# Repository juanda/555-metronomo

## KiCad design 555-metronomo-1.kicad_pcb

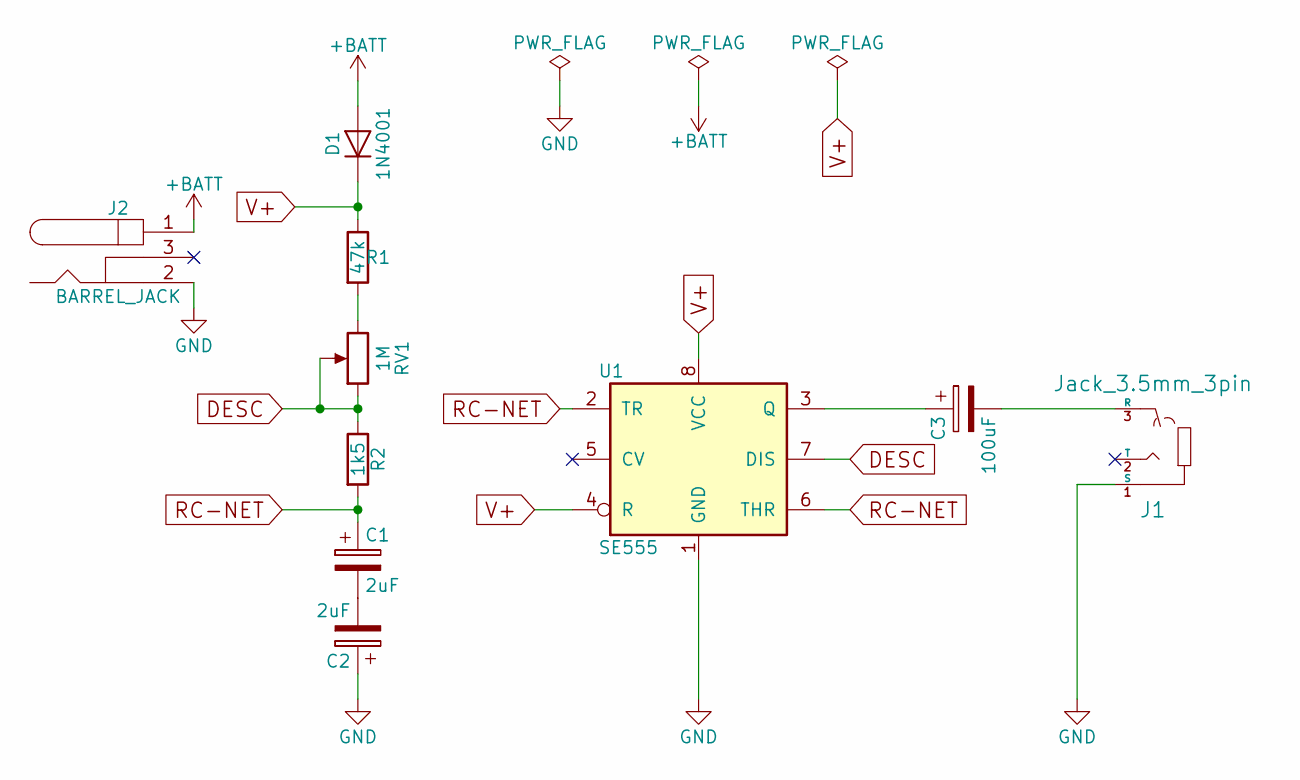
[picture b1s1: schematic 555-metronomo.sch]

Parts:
C1, C2: 2uF; CP_Axial_L18.0mm_D6.5mm_P25.00mm_Horizontal
C3: 100uF; CP_Axial_L34.5mm_D20.0mm_P41.00mm_Horizontal
D1: 1N4001; D_DO-41_SOD81_P5.08mm_Vertical_AnodeUp
J1: Jack_3.5mm_3pin; BARREL_JACK
J2: BARREL_JACK
R1: 47k; R_Axial_DIN0204_L3.6mm_D1.6mm_P1.90mm_Vertical
R2: 1k5; R_Axial_DIN0204_L3.6mm_D1.6mm_P1.90mm_Vertical
RV1: 1M; Potentiometer_Alps_RK09K_Horizontal
U1: SE555; DIP-8_W7.62mm

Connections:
+BATT: D1.2 (A), J2.1
DESC: R2.1, RV1.1, RV1.2, U1.7 (DIS)
GND: C2.1, J1.1 (S), J2.2, U1.1 (GND)
unnamed: C1.2, C2.2
unnamed: C3.1, U1.3 (Q)
unnamed: C3.2, J1.3 (R)
unnamed: R1.2, RV1.3
RC-NET: C1.1, R2.2, U1.2 (TR), U1.6 (THR)
V+: D1.1 (K), R1.1, U1.4 (R), U1.8 (VCC)

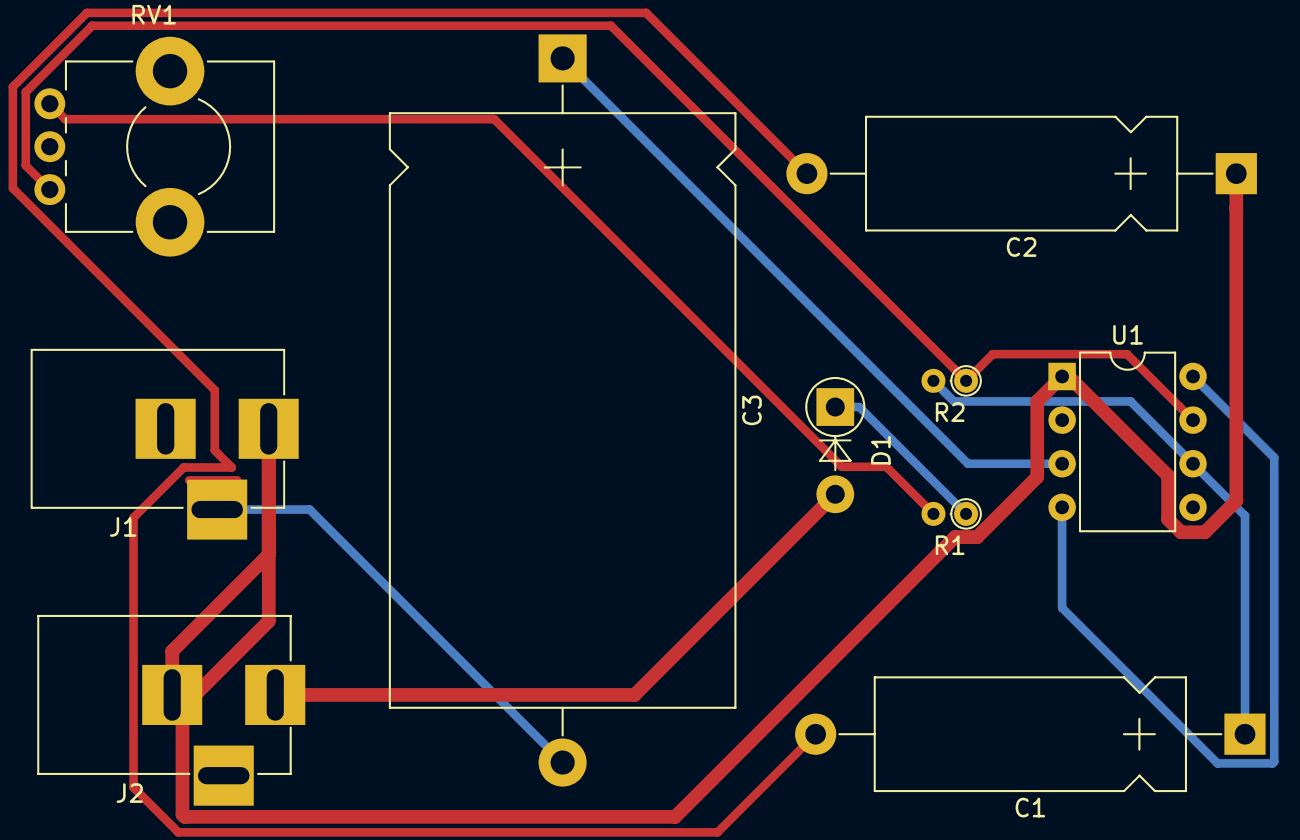
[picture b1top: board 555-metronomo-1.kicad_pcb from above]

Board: 2 copper layers, 10 parts (0 on the bottom side), 9 nets.

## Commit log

2017-05-03 commit inicial
2017-05-03 dos layouts
